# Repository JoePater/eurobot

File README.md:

# eurobot

This is the git repo for our Eurobot 2020 robot.

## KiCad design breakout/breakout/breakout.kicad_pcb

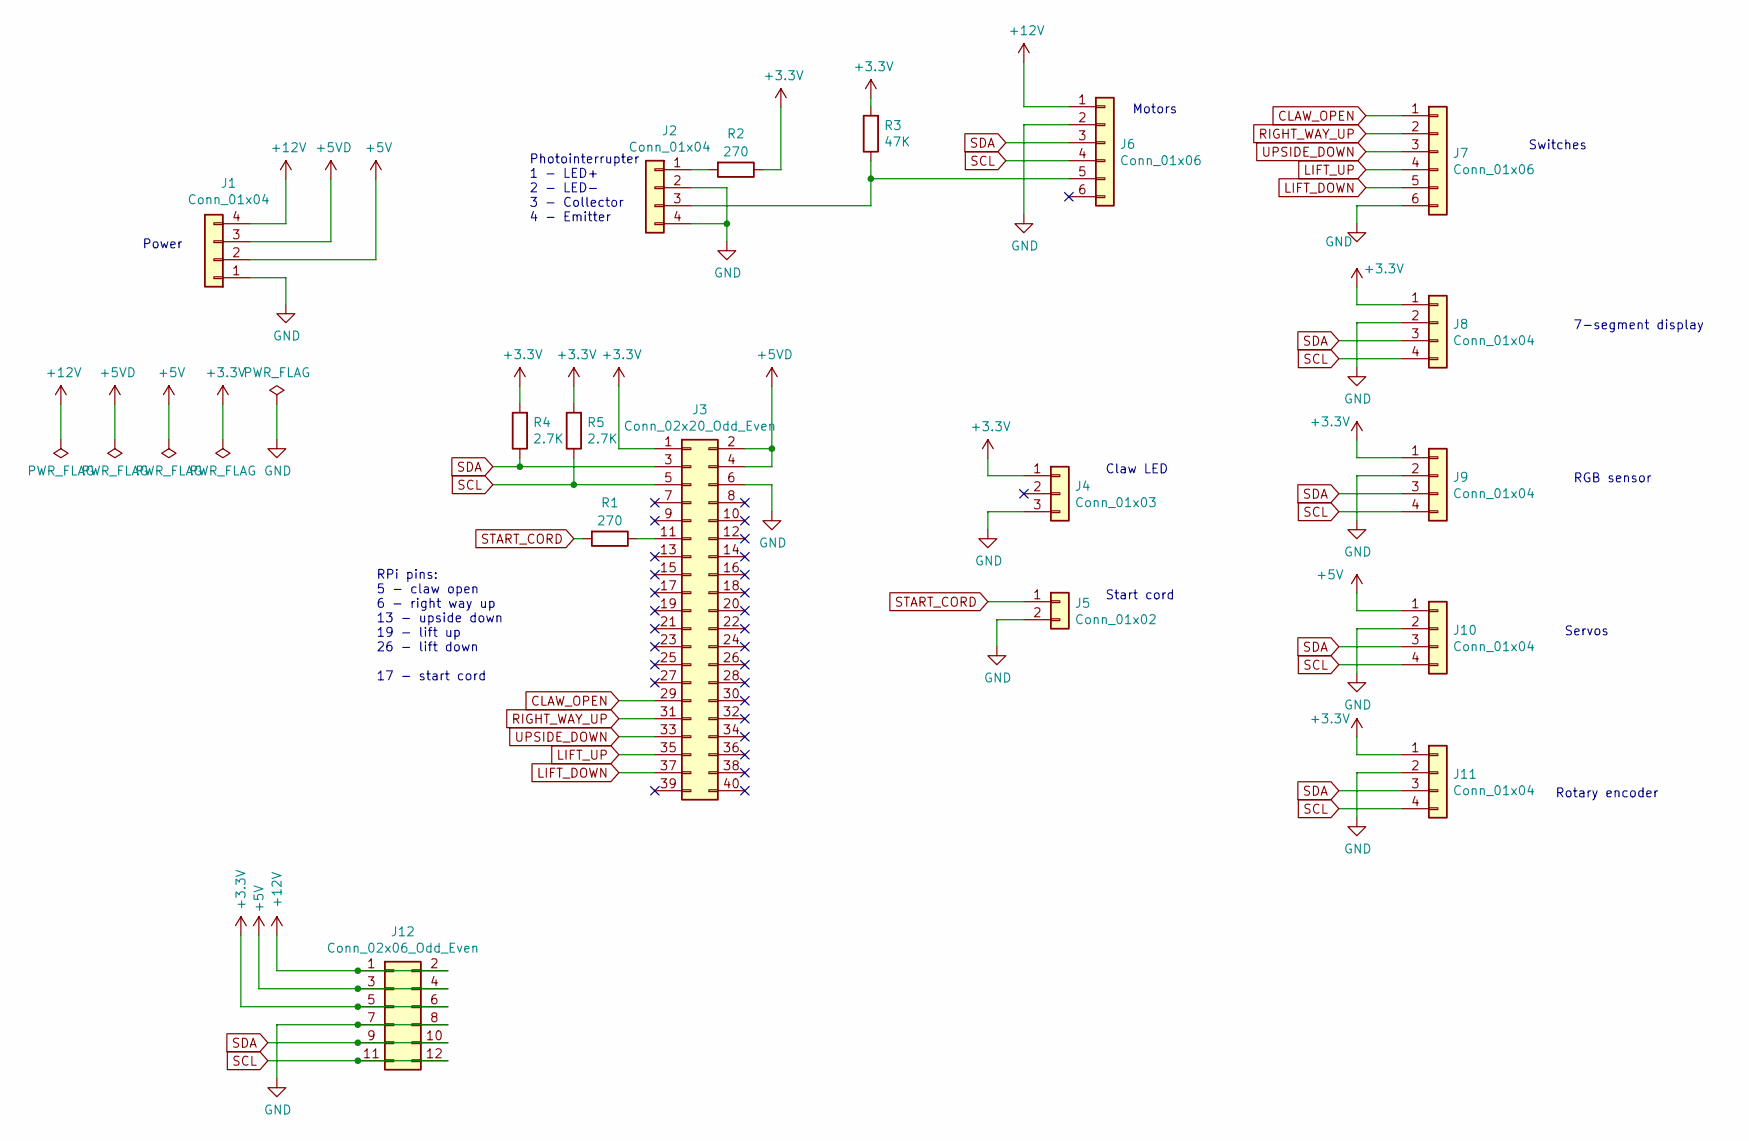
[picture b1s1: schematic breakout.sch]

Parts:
J1, J2, J8, J9, J10, J11: Conn_01x04; JST_EH_B4B-EH-A_1x04_P2.50mm_Vertical
J3: Conn_02x20_Odd_Even; PinHeader_2x20_P2.54mm_Vertical
J4: Conn_01x03; TE_Economy_power_1x3_P2.5mm_Vertical
J5: Conn_01x02; PinHeader_1x02_P2.54mm_Horizontal
J6, J7: Conn_01x06; JST_EH_B6B-EH-A_1x06_P2.50mm_Vertical
J12: Conn_02x06_Odd_Even; PinHeader_2x06_P2.54mm_Vertical
R1, R2: 270; R_0603_1608Metric
R3: 47K; R_0603_1608Metric
R4, R5: 2.7K; R_0603_1608Metric

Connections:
+3V3: J3.1, J4.1, J8.1, J9.1, J11.1, J12.5, J12.6, R2.1, R3.2, R4.2, R5.2
+5V: J1.2, J10.1, J12.3, J12.4
+5VD: J1.3, J3.2, J3.4
+12V: J1.4, J6.1, J12.1, J12.2
CLAW_OPEN: J3.29, J7.1
GND: J1.1, J2.2, J2.4, J3.6, J4.3, J5.2, J6.2, J7.6, J8.2, J9.2, J10.2, J11.2, J12.7, J12.8
LIFT_DOWN: J3.37, J7.5
LIFT_UP: J3.35, J7.4
unnamed: J2.1, R2.2
unnamed: J2.3, J6.5, R3.1
unnamed: J3.11, R1.1
RIGHT_WAY_UP: J3.31, J7.2
SCL: J3.5, J6.4, J8.4, J9.4, J10.4, J11.4, J12.11, J12.12, R5.1
SDA: J3.3, J6.3, J8.3, J9.3, J10.3, J11.3, J12.9, J12.10, R4.1
START_CORD: J5.1, R1.2
UPSIDE_DOWN: J3.33, J7.3

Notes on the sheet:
Switches
7-segment display
RGB sensor
Servos
Rotary encoder
Photointerrupter 1 - LED+ 2 - LED- 3 - Collector 4 - Emitter
Motors
Claw LED
Start cord
Power
RPi pins: 5 - claw open 6 - right way up 13 - upside down 19 - lift up 26 - lift down 17 - start cord

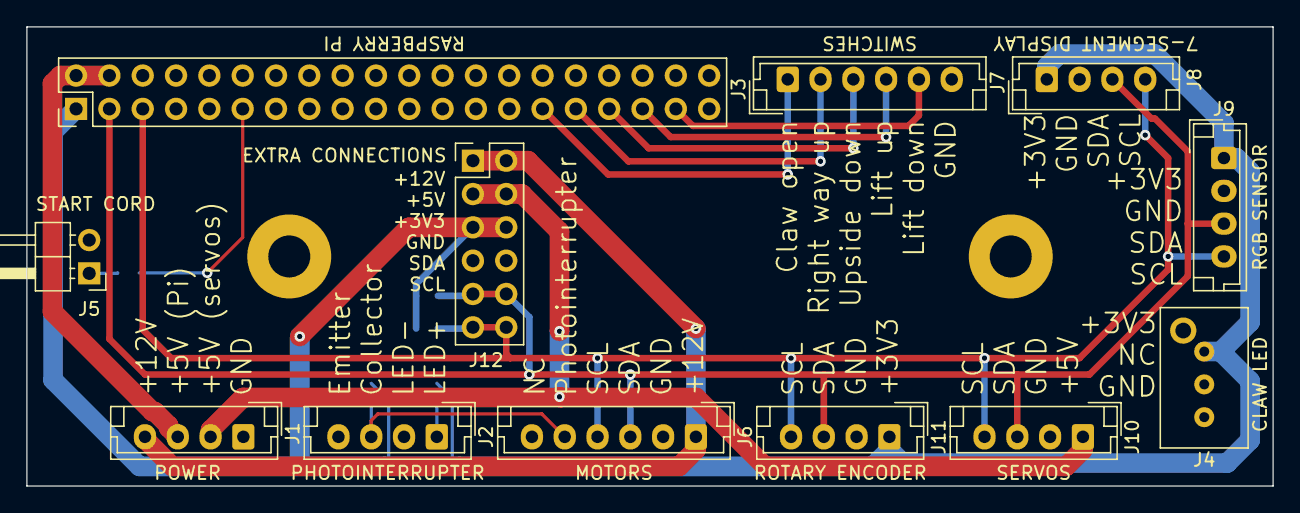
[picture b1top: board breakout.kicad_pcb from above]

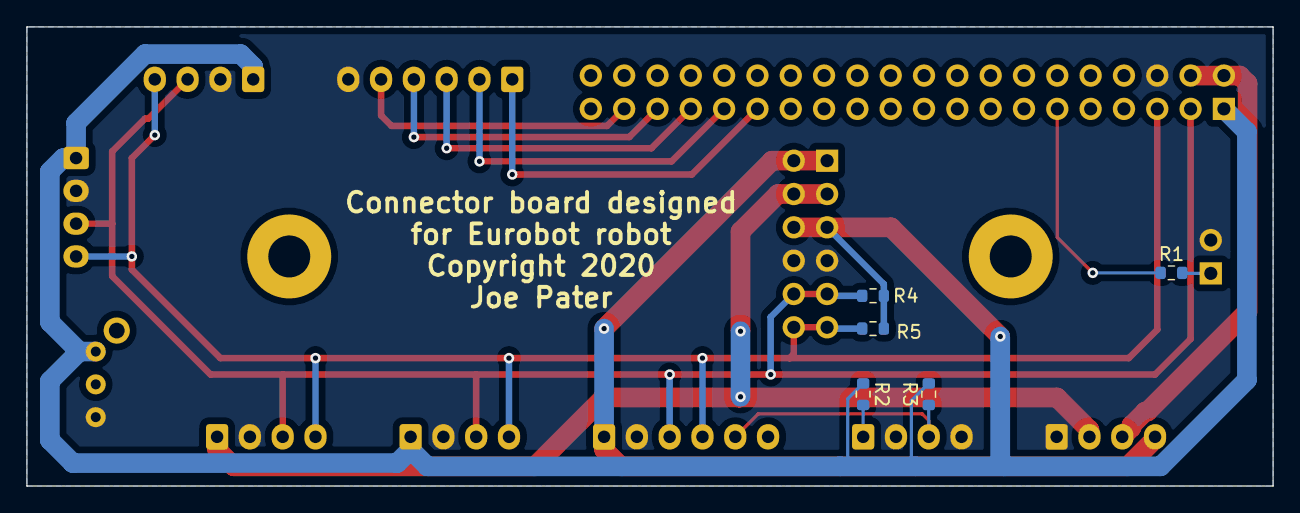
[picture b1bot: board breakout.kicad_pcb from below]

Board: 2 copper layers, 95.0 x 35.0 mm, 17 parts (5 on the bottom side), 16 nets.

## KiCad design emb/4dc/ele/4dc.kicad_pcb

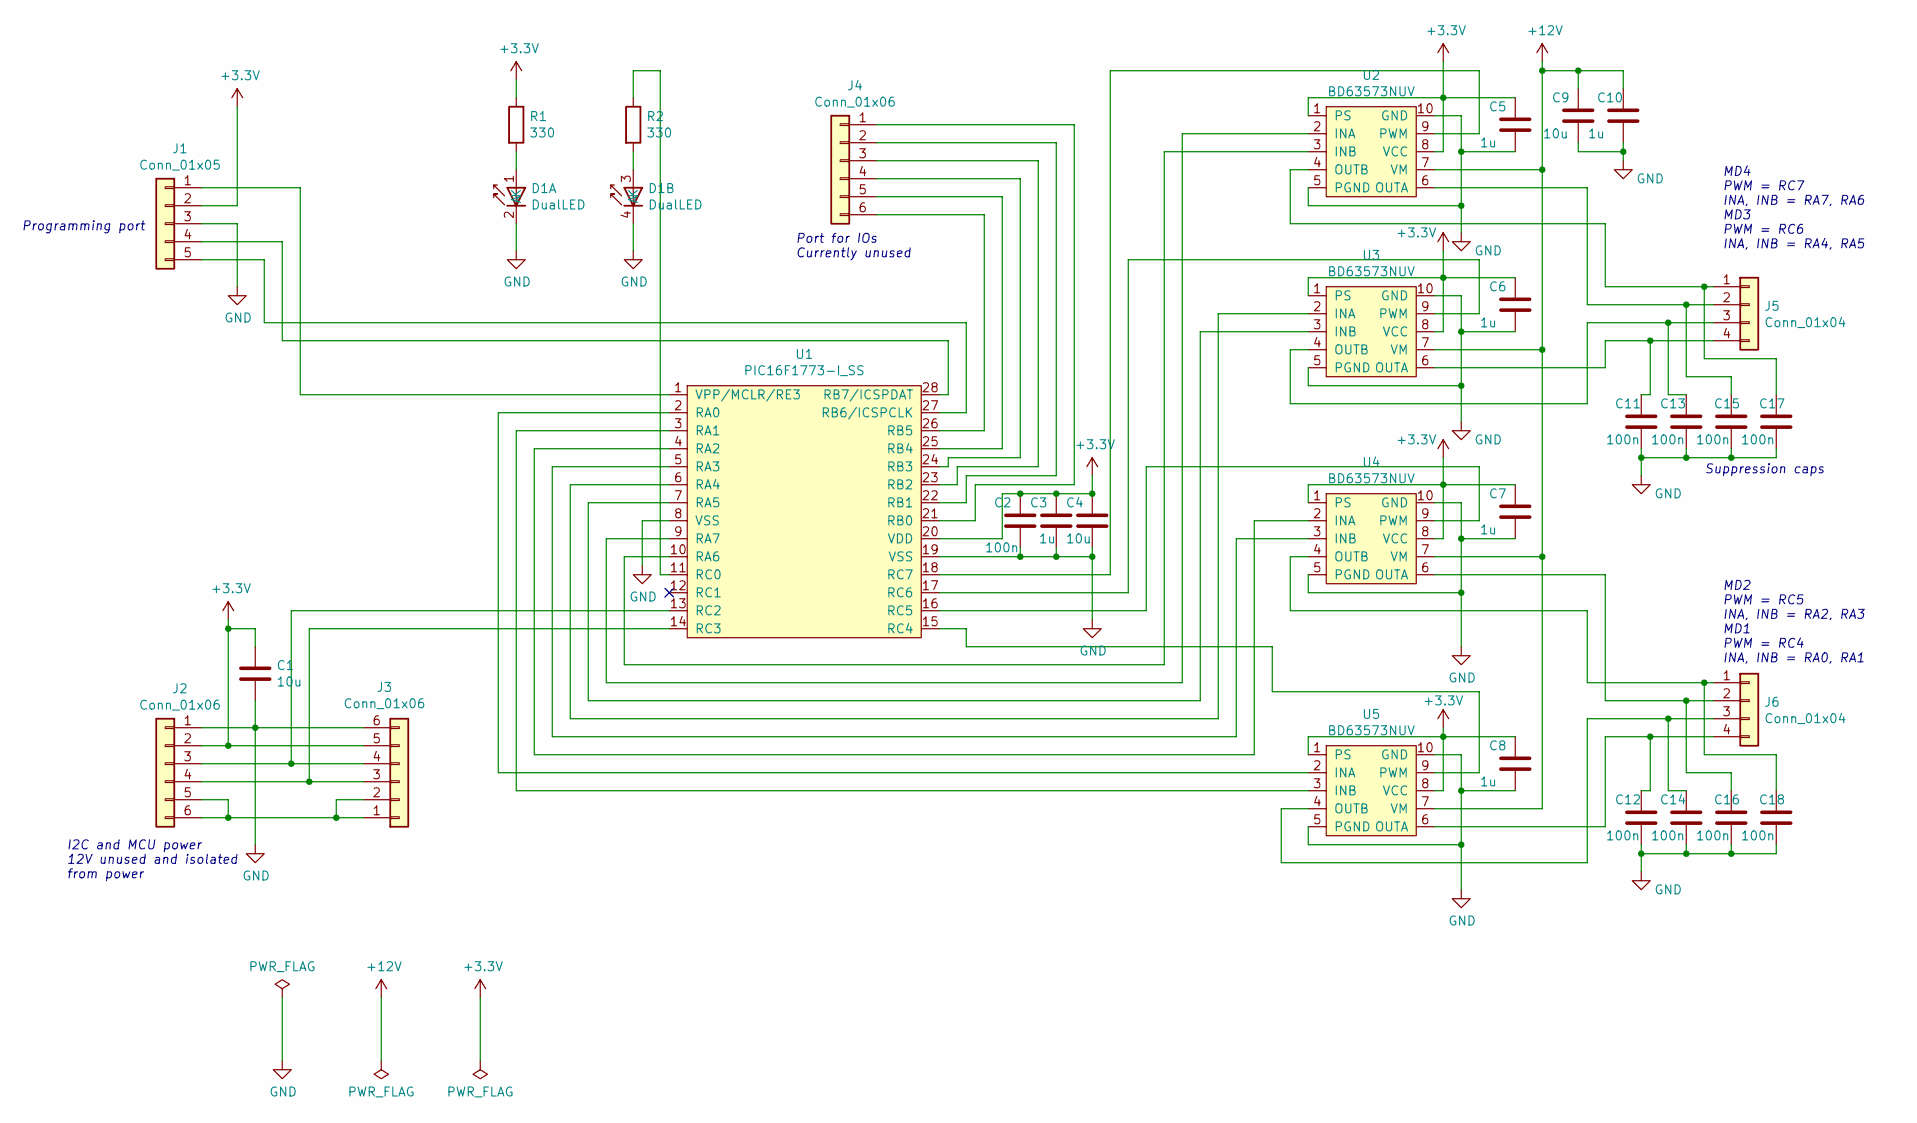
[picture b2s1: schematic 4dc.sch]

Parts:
C1, C4, C9: 10u; C_0805_2012Metric
C2, C11, C12, C13, C14, C15, C16, C17, C18: 100n; C_0603_1608Metric
C3, C5, C6, C7, C8, C10: 1u; C_0603_1608Metric
D1: DualLED; LED_0606
J1: Conn_01x05; PinHeader_1x05_P2.54mm_Vertical
J2, J3, J4: Conn_01x06; Molex_Micro-lock_1x06
J5, J6: Conn_01x04; Hirose_DF3EA-04P-2H_1x04-1MP_P2.00mm_Horizontal
R1, R2: 330; R_0603_1608Metric
U1: PIC16F1773-I_SS; SSOP-28_5.3x10.2mm_P0.65mm
U2, U3, U4, U5: BD63573NUV; VSON-10-1EP_3x3mm_P0.5mm_EP1.2x2mm

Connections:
+3V3: C1.1, C2.1, C3.1, C4.1, C5.1, C6.1, C7.1, C8.1, J1.2, J2.2, J3.5, R1.1, U1.20 (VDD), U2.1 (PS), U2.8 (VCC), U3.1 (PS), U3.8 (VCC), U4.1 (PS), U4.8 (VCC), U5.1 (PS), U5.8 (VCC)
+12V: C9.1, C10.1, U2.7 (VM), U3.7 (VM), U4.7 (VM), U5.7 (VM); also elsewhere on the board
GND: C1.2, C2.2, C3.2, C4.2, C5.2, C6.2, C7.2, C8.2, C9.2, C10.2, C11.2, C12.2, C13.2, C14.2, C15.2, C16.2, C17.2, C18.2, D1.2 (K), D1.4 (K), J1.3, J2.1, J3.6, U1.8 (VSS), U1.19 (VSS), U2.5 (PGND), U2.10 (GND), U3.5 (PGND), U3.10 (GND), U4.5 (PGND), U4.10 (GND), U5.5 (PGND), U5.10 (GND); also elsewhere on the board
unnamed: C11.1, J5.4, U3.6 (OUTA)
unnamed: C12.1, J6.4, U5.6 (OUTA)
unnamed: C13.1, J5.3, U3.4 (OUTB)
unnamed: C14.1, J6.3, U5.4 (OUTB)
unnamed: C15.1, J5.2, U2.6 (OUTA)
unnamed: C16.1, J6.2, U4.6 (OUTA)
unnamed: C17.1, J5.1, U2.4 (OUTB)
unnamed: C18.1, J6.1, U4.4 (OUTB)
unnamed: D1.1 (A), R1.2
unnamed: D1.3 (A), R2.2
unnamed: J1.1, U1.1 (VPP/MCLR/RE3)
unnamed: J1.4, U1.28 (RB7/ICSPDAT)
unnamed: J1.5, U1.27 (RB6/ICSPCLK)
unnamed: J2.3, J3.4, U1.13 (RC2)
unnamed: J2.4, J3.3, U1.14 (RC3)
unnamed: J2.5, J2.6, J3.1, J3.2
unnamed: J4.1, U1.21 (RB0)
unnamed: J4.2, U1.22 (RB1)
unnamed: J4.3, U1.23 (RB2)
unnamed: J4.4, U1.24 (RB3)
unnamed: J4.5, U1.25 (RB4)
unnamed: J4.6, U1.26 (RB5)
unnamed: R2.1, U1.11 (RC0)
unnamed: U1.2 (RA0), U5.2 (INA)
unnamed: U1.3 (RA1), U5.3 (INB)
unnamed: U1.4 (RA2), U4.2 (INA)
unnamed: U1.5 (RA3), U4.3 (INB)
unnamed: U1.6 (RA4), U3.2 (INA)
unnamed: U1.7 (RA5), U3.3 (INB)
unnamed: U1.9 (RA7), U2.2 (INA)
unnamed: U1.10 (RA6), U2.3 (INB)
unnamed: U1.15 (RC4), U5.9 (PWM)
unnamed: U1.16 (RC5), U4.9 (PWM)
unnamed: U1.17 (RC6), U3.9 (PWM)
unnamed: U1.18 (RC7), U2.9 (PWM)

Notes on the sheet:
Port for IOs Currently unused
Programming port
I2C and MCU power 12V unused and isolated from power
Suppression caps
MD2 PWM = RC5 INA, INB = RA2, RA3 MD1 PWM = RC4 INA, INB = RA0, RA1
MD4 PWM = RC7 INA, INB = RA7, RA6 MD3 PWM = RC6 INA, INB = RA4, RA5

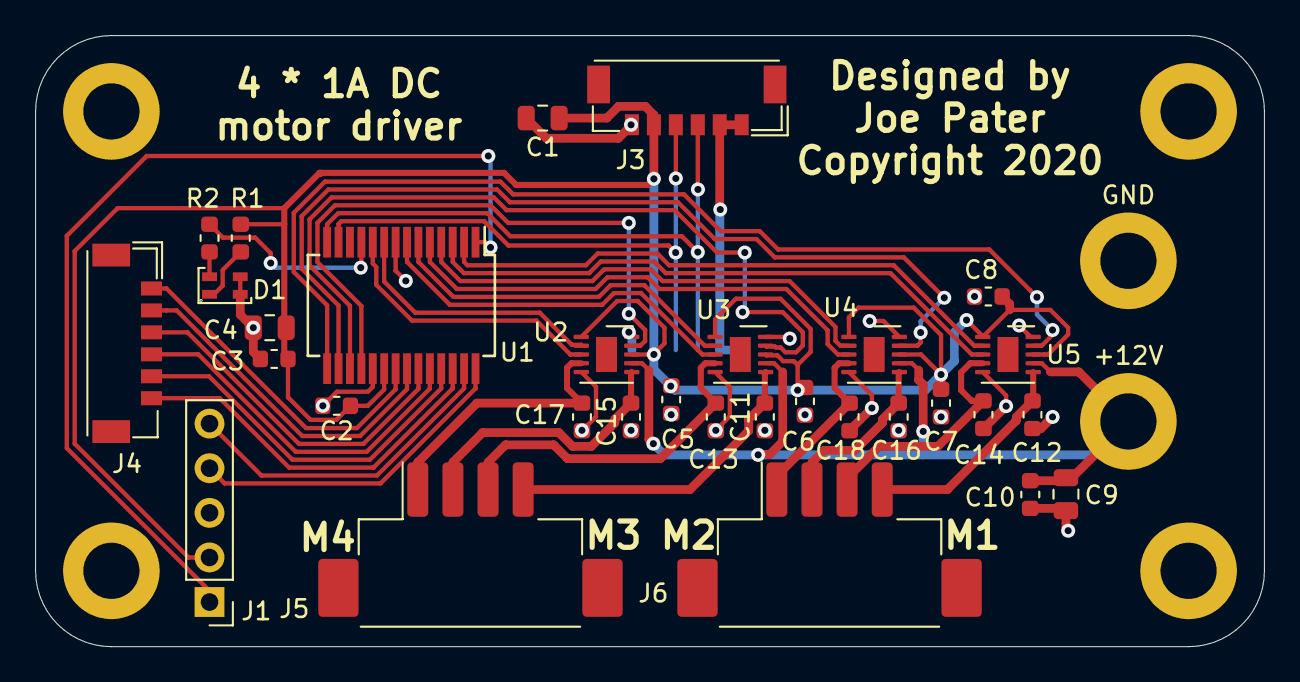
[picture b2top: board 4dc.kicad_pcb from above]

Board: 2 copper layers, 70.0 x 34.8 mm, 35 parts (1 on the bottom side), 38 nets.

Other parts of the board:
+12V: MountingHole_3.2mm_M3_ISO14580_Pad
GND: MountingHole_3.2mm_M3_ISO14580_Pad
GND#2: MountingHole_3.2mm_M3_ISO14580_Pad

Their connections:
+12V: +12V.1; also elsewhere on the board
GND: GND.1, GND#2.1; also elsewhere on the board

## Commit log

2020-05-13 Init
2020-05-13 Test
2020-05-14 Progress on claw arm
2020-05-15 Worked on big gear for claw
2020-05-15 Put claw into single model
2020-06-17 Changed claw
2020-06-23 Started interface definition
2020-06-24 Changed interface
2020-06-26 Designed revolver with bearing
2020-06-29 Worked on revolver, python interface v0.2
2020-06-29 Wrote python interface v0.3
2020-06-29 Rearranged directories
2020-06-29 Added python files
2020-07-12 Worked on revolver and claw
2020-07-14 Made checklist and plan of journey
2020-07-14 Fixed merge
2020-07-14 Added description of journey
2020-07-14 Fixed table
2020-07-14 Worked on revolver, started drive
2020-07-18 Designed drive base
2020-07-20 Worked on lots of CAD
2020-07-20 added drop bouys
2020-07-21 Fixed name, fixed indent
2020-07-21 Worked on cad
2020-07-24 Worked on rotary encoder code
2020-07-24 Made cable hole wider
2020-08-02 Begun working on skeleton
2020-08-02 Worked on ultrasound
2020-08-02 Moved python interface to version 0.4
2020-08-02 Made rotary encoder clamp fit better
2020-08-02 Made photointerrupter parts
2020-08-02 Adjusted drive
2020-08-03 Nothing major
2020-08-03 Added crude map showing axis
2020-08-03 Added version 0.5
2020-08-03 Wrote main functions of buoys module (in meeting)
2020-08-05 Begun route.py
2020-08-05 Finished first draft
2020-08-07 Made gcode for most parts to be printed
2020-08-07 Made flag,platform
2020-08-10 Started revolver servo code
2020-08-13 Tweaks
2020-08-16 Created motor test file
2020-08-16 Finished test code for motors and servos
2020-08-22 Imported rot to mplabx
2020-08-22 Added rotary tests
2020-08-22 Fixed rot address
2020-08-22 Got rotary encoder working!!!!!
2020-08-23 Fixed servos address
2020-08-23 Fixed global ref
2020-08-23 Moved to v0.6
    -Removed most asynchronous functions
    -Moved some functions to use Pt
2020-08-23 Made side markers
2020-08-23 Got servo driver working
2020-08-23 Finished off route + revolver code from meeting
2020-08-25 Finished move.py, done most of claw.py
2020-08-25 Worked on fourth wheel
2020-08-30 Corrected motors address
2020-08-30 Fixed comma
2020-08-30 Fixed bug
2020-08-30 Fixed rounding
2020-08-30 Fixed enable shift
2020-09-01 Finished other wheel
2020-09-01 Fixed magnet locations
2020-09-01 Implemented revolver i2c
2020-09-01 Worked on paths
2020-09-01 Worked on 4dc
2020-09-14 Added file for accessing buttons
2020-09-14 Got 4dc working with photointerrupter
2020-09-14 Fucking MPLABX pretending to change files
2020-09-14 Added location.opponent()
2020-09-14 Begun location file
2020-09-14 Changed opposition to opponent
2020-09-14 Written cpp interface
2020-09-14 Build directory for python module
2020-09-14 Begun some cpp files
2020-09-14 Setup file for python module build/install
2020-09-14 Cancelled :-(
2020-10-22 Begun debugger code
2020-10-22 Got FunctionQueue working
2020-10-26 Fucking MPLAB pretending stuff's changed. NOTHING HAS CHANGEDgit status!
2020-11-01 Wrote variable-tracker.py to synchronize access to shared variables between GUI and robot code
2020-11-01 Renamed files so that they can be imported
2020-11-01 written dictionary label
2020-11-02 Modified funcQueue.py to add support for the VariableTracker
2020-11-03 Added diagram
2020-11-04 Wrote codeRunner.py, working
2020-11-04 fixed incorrect method names
2020-11-04 added __pycache__ to .gitignore
2020-11-07 Created FunctionQueueWidget class
    It will display information about a FunctionQueue, useful for debugging
2020-11-07 Ignore __pycache__
2020-11-08 testing
2020-11-08 added slider
2020-11-08 Revert "testing"
    This reverts commit a9e3ae1e6a91c69ddc1823fd0f13c79eb8934dd5.
2020-11-08 implemented function queue
2020-11-08 Modified RobotSlider to use a Frame
2020-11-08 Changed CodeRunner to have grid() and pack() methods
2020-11-08 Written main window code
2020-11-15 added frame functions to classes
2020-11-15 Fixed use of Frame in RobotButton and RobotLabel
2020-11-15 Creating new class RObotiinputs
2020-11-15 changed main window
2020-11-20 Error fixes, and moved test code into function
2020-11-20 Fixed some errors, moved tests into function
2020-11-20 Adjusted to take a function queue parameter that is used for all widgets
2020-11-20 Error fixes
2020-11-20 Error fixes, wrote test
2020-11-20 Wrote code to simulate robot
2020-11-20 Checked over and tweaked lots of files. Made status.org to keep track of progress on code
2020-12-06 Changed around code
2020-12-06 Removed f-string, since the pi is on an earlier python version
2020-12-06 Wrote initial main debugging GUI
2020-12-27 Made motors accurate
2020-12-27 Made breakout board
2020-12-27 mplab
2020-12-27 GUI working with options for motors or buttons or revolver
2020-12-27 Updated lost changes to motors and buttons

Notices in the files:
breakout/breakout/breakout.kicad_pcb:
Copyright 2020
